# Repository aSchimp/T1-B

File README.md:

T1-B
====

T1-B = Turtle Bot 1

Installation
====

This *must* be run on a BeagleBone Black running the Debian operating system.  Get the latest image from: http://beagleboard.org/latest-images. The image used for testing was dated 2014-04-23. To check the version installed use

````
cat /boot/uboot/ID.txt
````

Make sure you can establish an SSH connection to the BeagleBone Black. Also make sure that the BBB has a persistant internet connection, either through an ethernet connection or through a USB connection to your computer.

### Setting up a persistant USB internet connection

The steps below are for Windows.

* Open the control panel, and search for "network connections" in the search box. Click "View Network Connections" in the results.
* Right-click the internet connection to share with the BeagleBone Black and select Properties. Navigate to the Sharing tab.
* Select the option to "Allow other network users to connect through this computer's Internet connection"
* Select the BeagleBone Black's network connection from the dropdown and then click OK.
* Now go back to Network Connections and right click the BeagleBone Black's network connection, and select Properties.
* Click "Internet Protocol Version 4 (TCP/IPv4)" in the list and select Properties
* Select the options to "Obtain an IP address automatically" and "obtain DNS server address automatically", and click OK

On the BeagleBone Black run the following commands

````
route add default gw 192.168.7.1
echo "nameserver 8.8.8.8" >> /etc/resolv.conf
````

Test the connection by running `ping google.com`.

Run the following command.

````
nano /opt/scripts/boot/am335x_evm.sh
````

Scroll down until you see the following lines

````
/sbin/ifconfig usb0 192.168.7.2 netmask 255.255.255.252
/usr/sbin/udhcpd -S /etc/udhcpd.conf
````

Immediately after those lines, add the following:

````
/sbin/route add default gw 192.168.7.1 metric 1
````

While you're editing that file, add the following line as well (beneath the line just added). This will allow the WiFi connection which will be setup by the installation script to work on startup. Replace 192.168.1.1 with the IP address of your router. You can find this by running `ipconfig` from a command prompt in Windows. Look for the default gateway for the wireless network connection.

````
/sbin/route add default gw 192.168.1.1 metric 2
````

Thanks to [Carl Lance](http://lanceme.blogspot.com/2013/06/windows-7-internet-sharing-for.html) for the pointers on getting this to work.

### Optionally Disable HDMI

TODO: Add an explanation here

https://learn.adafruit.com/setting-up-wifi-with-beaglebone-black/hardware

### Install Git

````
ntpdate -b -s -u pool.ntp.org
apt-get update && apt-get install git
````

### Install T1-B Software

Shutdown the BBB and plug in the USB wifi adapter. Use a WiFi adapter from [this list](http://www.elinux.org/Beagleboard:BeagleBoneBlack#WIFI_Adapters) for best results. The T1-B installation script has only been tested with the [NETGEAR N150 Wi-Fi USB Adapter (WNA1100)](http://www.amazon.com/gp/product/B0036R9XRU/ref=oh_aui_detailpage_o02_s00?ie=UTF8&psc=1). Turn the device back on.

Clone this repository into {TODO: determine best directory} using the following command.

````
cd {TODO: put directory here}
git clone https://github.com/aschimp/t1-b
````

Place your WiFi network SSID and password into the settings.cfg file.

````
cd t1-b/setup
nano settings.cfg
````

Finally, run the install script. The system will reboot several times during the installation. Log messages after rebooting will be sent to the install_log.txt file in the t1-b/setup directory.

````
chmod +x *.sh
./install.sh
````

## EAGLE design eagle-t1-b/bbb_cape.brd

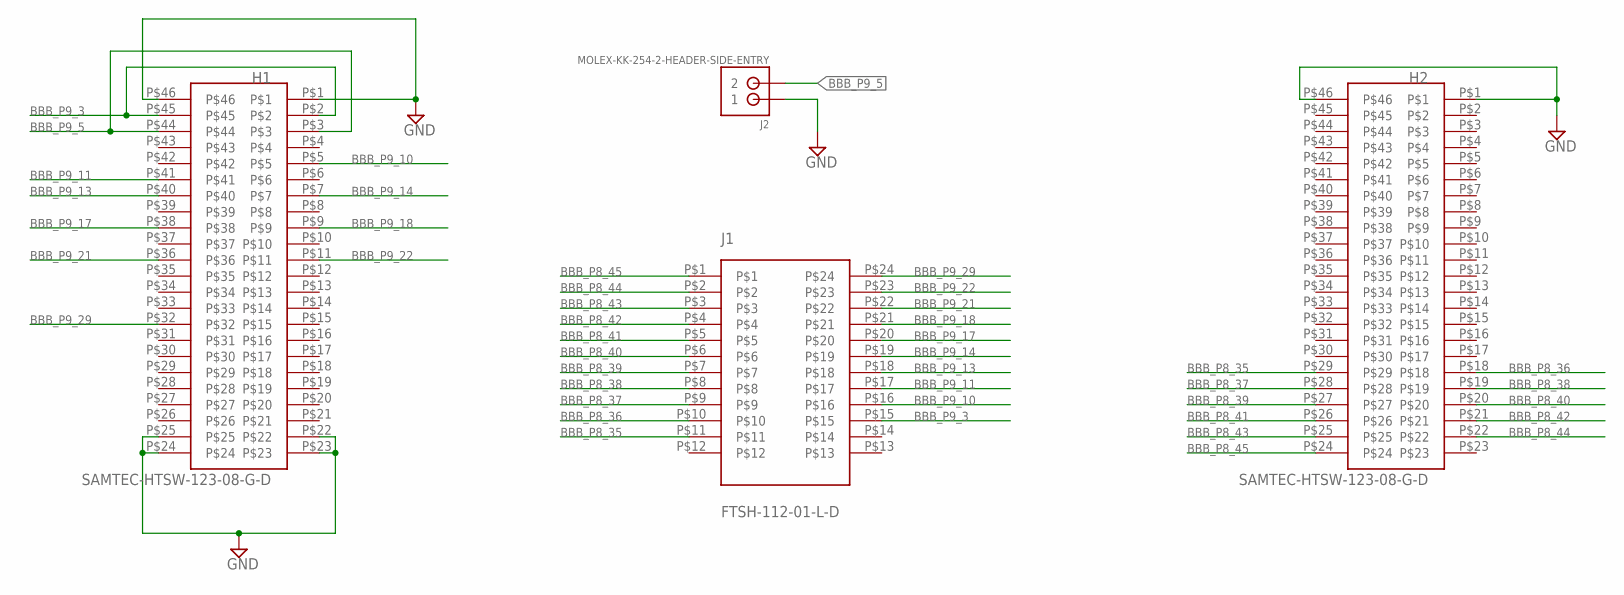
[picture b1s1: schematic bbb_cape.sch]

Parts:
H1, H2: SAMTEC-HTSW-123-08-G-D; HEADER-2X23-0.1-INCH
J1: FTSH-112-01-L-D
J2: MOLEX-KK-254-2-HEADER-SIDE-ENTRY

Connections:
BBB_P8_35: H2.P$29, J1.P$11
BBB_P8_36: H2.P$18, J1.P$10
BBB_P8_37: H2.P$28, J1.P$9
BBB_P8_38: H2.P$19, J1.P$8
BBB_P8_39: H2.P$27, J1.P$7
BBB_P8_40: H2.P$20, J1.P$6
BBB_P8_41: H2.P$26, J1.P$5
BBB_P8_42: H2.P$21, J1.P$4
BBB_P8_43: H2.P$25, J1.P$3
BBB_P8_44: H2.P$22, J1.P$2
BBB_P8_45: H2.P$24, J1.P$1
BBB_P9_3: H1.P$2, H1.P$45, J1.P$15
BBB_P9_5: H1.P$3, H1.P$44, J2.P$2 (2)
BBB_P9_10: H1.P$5, J1.P$16
BBB_P9_11: H1.P$41, J1.P$17
BBB_P9_13: H1.P$40, J1.P$18
BBB_P9_14: H1.P$7, J1.P$19
BBB_P9_17: H1.P$38, J1.P$20
BBB_P9_18: H1.P$9, J1.P$21
BBB_P9_21: H1.P$36, J1.P$22
BBB_P9_22: H1.P$11, J1.P$23
BBB_P9_29: H1.P$32, J1.P$24
GND: H1.P$1, H1.P$22, H1.P$23, H1.P$24, H1.P$25, H1.P$46, H2.P$1, H2.P$46, J2.P$1 (1)

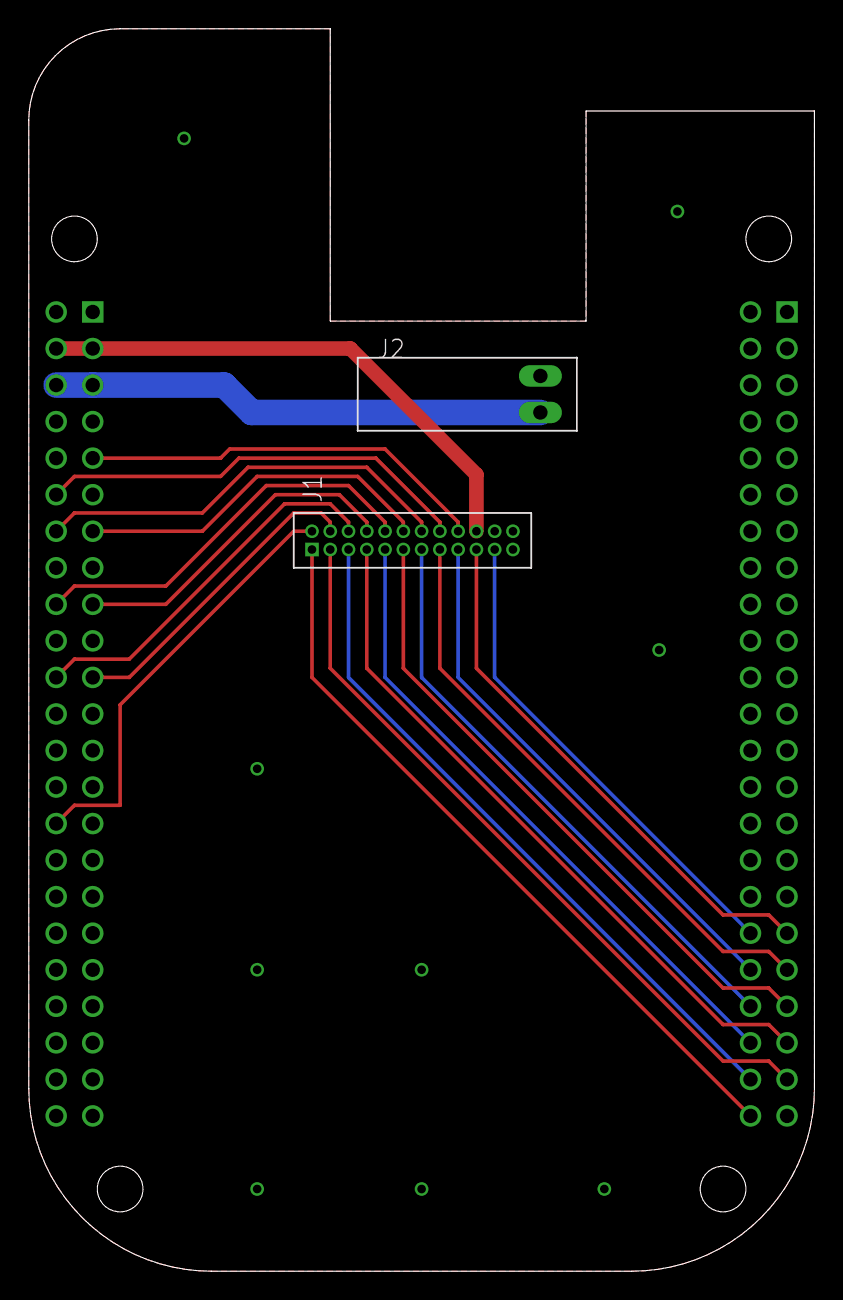
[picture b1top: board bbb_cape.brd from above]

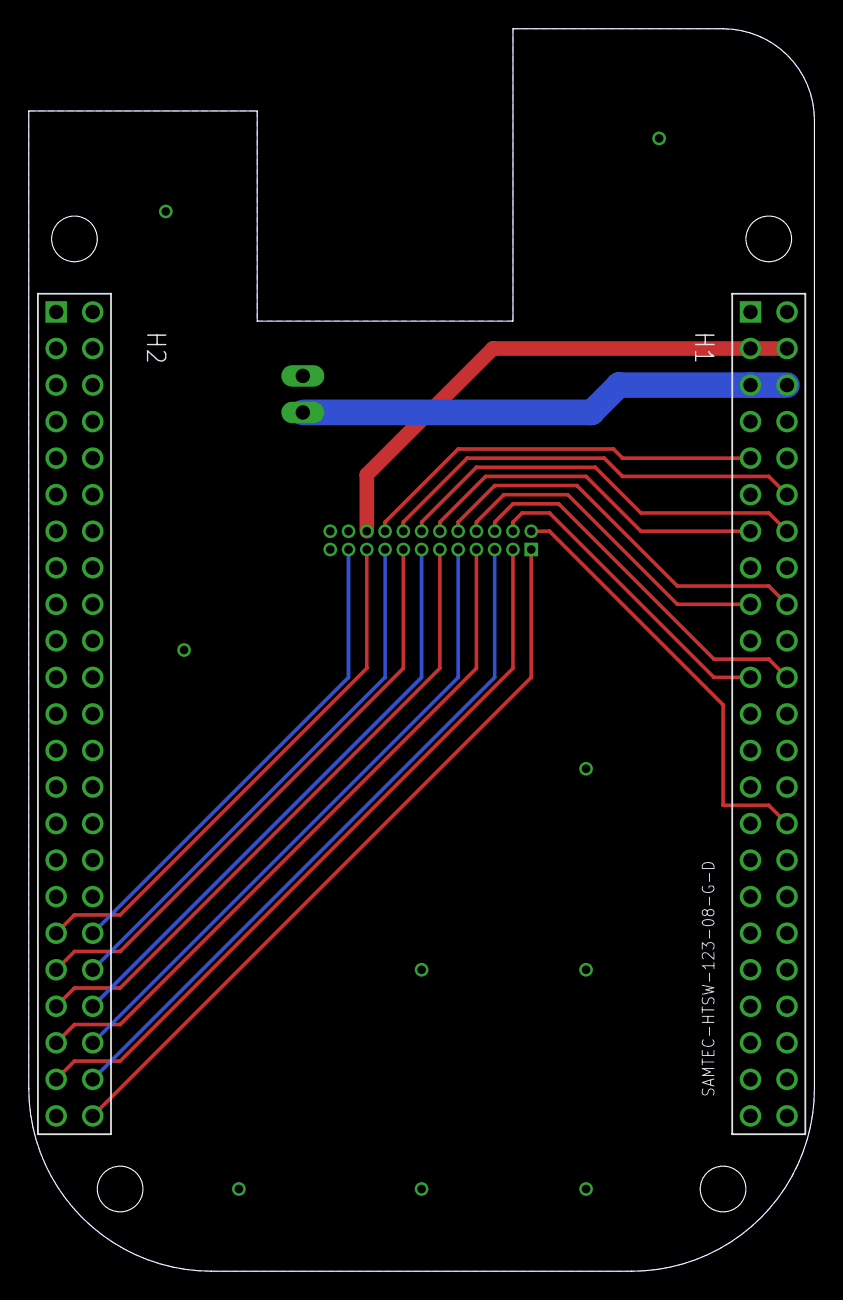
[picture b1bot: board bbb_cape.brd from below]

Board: 2 copper layers, 54.6 x 86.4 mm, 4 parts (2 on the bottom side), 23 nets.

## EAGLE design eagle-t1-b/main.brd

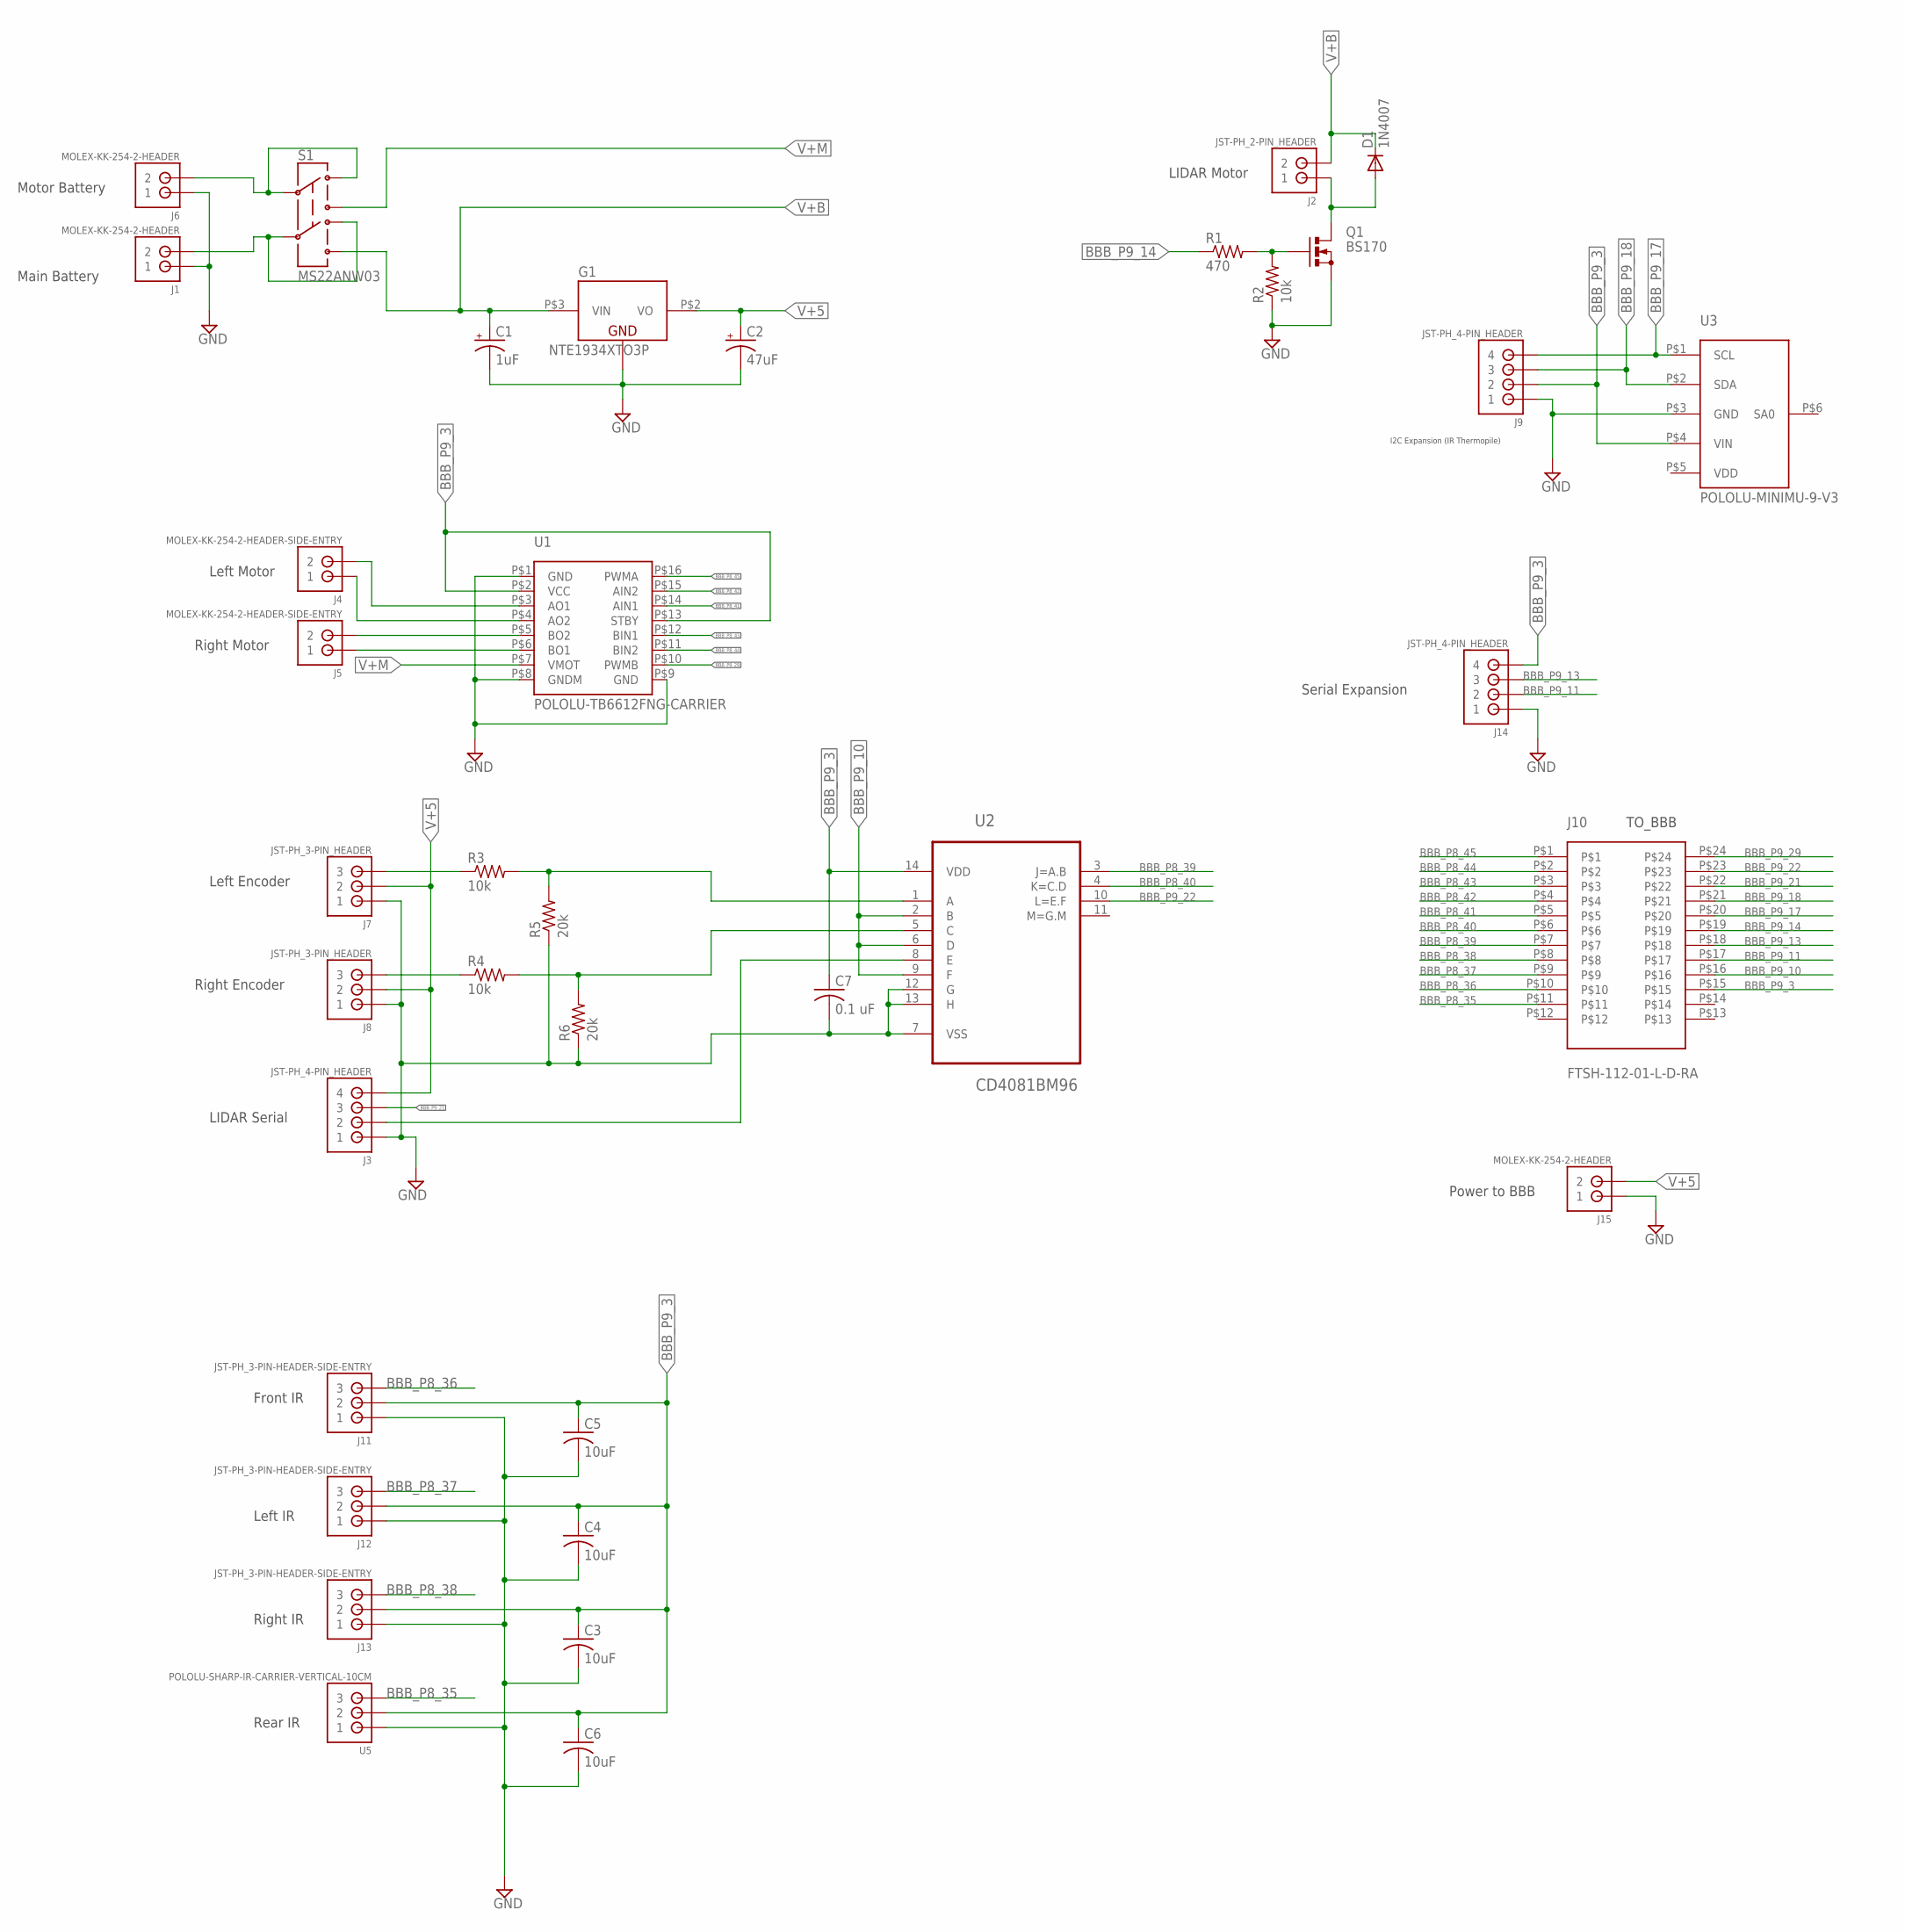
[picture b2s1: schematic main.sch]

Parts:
C1: 1uF; PANASONIC_B
C2: 47uF; PANASONIC_C
C3, C4, C5, C6: 10uF; C0603
C7: 0.1 uF; C0603
D1: 1N4007; DO41-10
G1: NTE1934XTO3P; TO3P
J1, J6, J15: MOLEX-KK-254-2-HEADER
J2: JST-PH_2-PIN_HEADER; JST_B2B-PH_HEADER
J3, J9, J14: JST-PH_4-PIN_HEADER; JST_B4B-PH_HEADER
J4, J5: MOLEX-KK-254-2-HEADER-SIDE-ENTRY
J7, J8: JST-PH_3-PIN_HEADER; JST_B3B-PH_HEADER
J10: FTSH-112-01-L-D-RA
J11, J12, J13: JST-PH_3-PIN-HEADER-SIDE-ENTRY; JST-S3B-PH-K-S
Q1: BS170; SOT54E
R1: 470; R0402
R2, R3, R4: 10k; R0402
R5, R6: 20k; R0402
S1: MS22ANW03; SWITCH-DPDT-NKK-MS22ANW03
U1: POLOLU-TB6612FNG-CARRIER
U2: CD4081BM96; SO14
U3: POLOLU-MINIMU-9-V3
U5: POLOLU-SHARP-IR-CARRIER-VERTICAL-10CM; POLOLU-SHARP-IR-CARRIER-VERTICAL-GP2Y0D8**Z0F

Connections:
BBB_P8_35: J10.P$11, U5.P$3 (3)
BBB_P8_36: J10.P$10, J11.P$3 (3)
BBB_P8_37: J10.P$9, J12.P$3 (3)
BBB_P8_38: J10.P$8, J13.P$3 (3)
BBB_P8_39: J10.P$7, U2.3 (J=A.B)
BBB_P8_39_AND_INPUT: R3.2, R5.2, U2.1 (A)
BBB_P8_40: J10.P$6, U2.4 (K=C.D)
BBB_P8_40_AND_INPUT: R4.2, R6.2, U2.5 (C)
BBB_P8_41: J10.P$5, U1.P$14 (AIN1)
BBB_P8_42: J10.P$4, U1.P$15 (AIN2)
BBB_P8_43: J10.P$3, U1.P$12 (BIN1)
BBB_P8_44: J10.P$2, U1.P$11 (BIN2)
BBB_P8_45: J10.P$1, U1.P$16 (PWMA)
BBB_P9_3: C3.1, C4.1, C5.1, C6.1, C7.1, J9.P2 (2), J10.P$15, J11.P$2 (2), J12.P$2 (2), J13.P$2 (2), J14.P4 (4), U1.P$2 (VCC), U1.P$13 (STBY), U2.14 (VDD), U3.P$4 (VIN), U5.P$2 (2)
BBB_P9_10: J10.P$16, U2.2 (B), U2.6 (D), U2.9 (F)
BBB_P9_11: J10.P$17, J14.P2 (2)
BBB_P9_13: J10.P$18, J14.P3 (3)
BBB_P9_14: J10.P$19, R1.1
BBB_P9_17: J9.P4 (4), J10.P$20, U3.P$1 (SCL)
BBB_P9_18: J9.P3 (3), J10.P$21, U3.P$2 (SDA)
BBB_P9_21: J3.P3 (3), J10.P$22
BBB_P9_22: J10.P$23, U2.10 (L=E.F)
BBB_P9_29: J10.P$24, U1.P$10 (PWMB)
GND: C1.-, C2.-, C3.2, C4.2, C5.2, C6.2, C7.2, G1.P$1 (GND), J1.P$1 (1), J3.P1 (1), J6.P$1 (1), J7.P1 (1), J8.P1 (1), J9.P1 (1), J11.P$1 (1), J12.P$1 (1), J13.P$1 (1), J14.P1 (1), J15.P$1 (1), Q1.S, R2.1, R5.1, R6.1, U1.P$1 (GND), U1.P$8 (GNDM), U1.P$9 (GND), U2.7 (VSS), U2.12 (G), U2.13 (H), U3.P$3 (GND), U5.P$1 (1)
unnamed: Q1.G, R1.2, R2.2
unnamed: D1.A, J2.P1 (1), Q1.D
unnamed: J5.P$1 (1), U1.P$6 (BO1)
unnamed: J5.P$2 (2), U1.P$5 (BO2)
unnamed: J4.P$1 (1), U1.P$4 (AO2)
unnamed: J4.P$2 (2), U1.P$3 (AO1)
unnamed: J7.P3 (3), R3.1
unnamed: J6.P$2 (2), S1.P$1 (1), S1.P$2 (2)
unnamed: J1.P$2 (2), S1.P$4 (4), S1.P$5 (5)
unnamed: J8.P3 (3), R4.1
unnamed: J3.P2 (2), U2.8 (E)
V+5: C2.+, G1.P$2 (VO), J3.P4 (4), J7.P2 (2), J8.P2 (2), J15.P$2 (2)
V+B: C1.+, D1.C, G1.P$3 (VIN), J2.P2 (2), S1.P$6 (6)
V+M: S1.P$3 (3), U1.P$7 (VMOT)
VDD: U3.P$5 (VDD)

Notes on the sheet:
Left Motor
Right Motor
Motor Battery
Main Battery
Left Encoder
Right Encoder
LIDAR Serial
LIDAR Motor
I2C Expansion (IR Thermopile)
TO_BBB
Serial Expansion
Front IR
Left IR
Right IR
Rear IR
Power to BBB

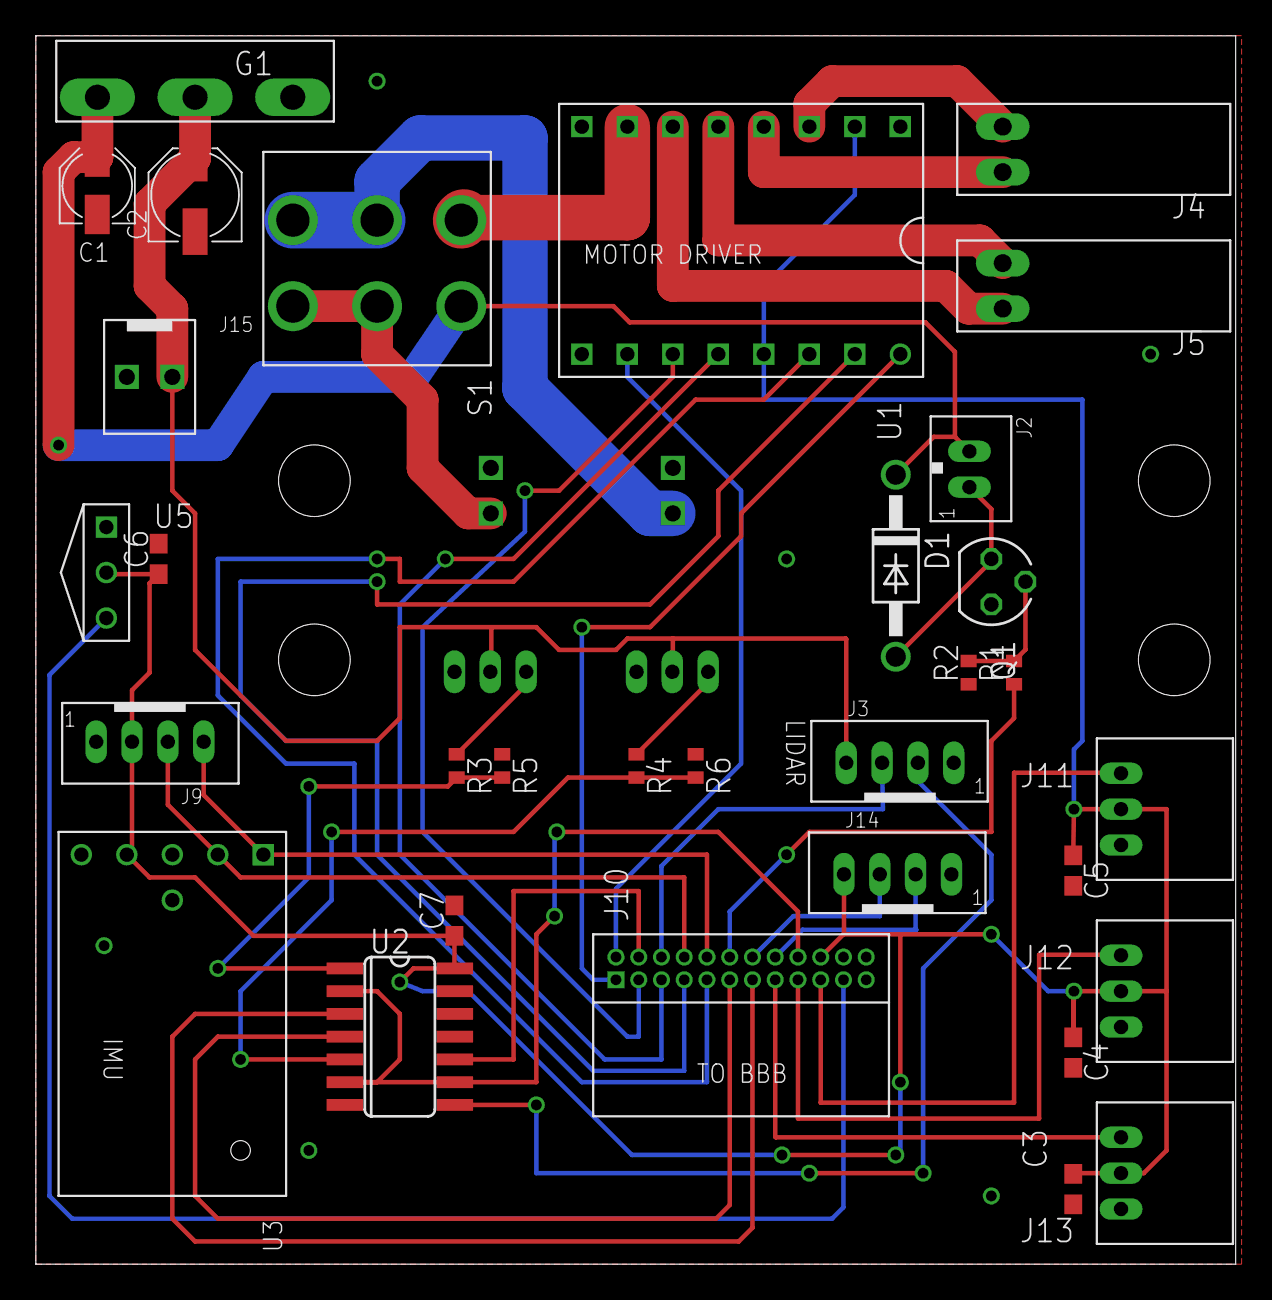
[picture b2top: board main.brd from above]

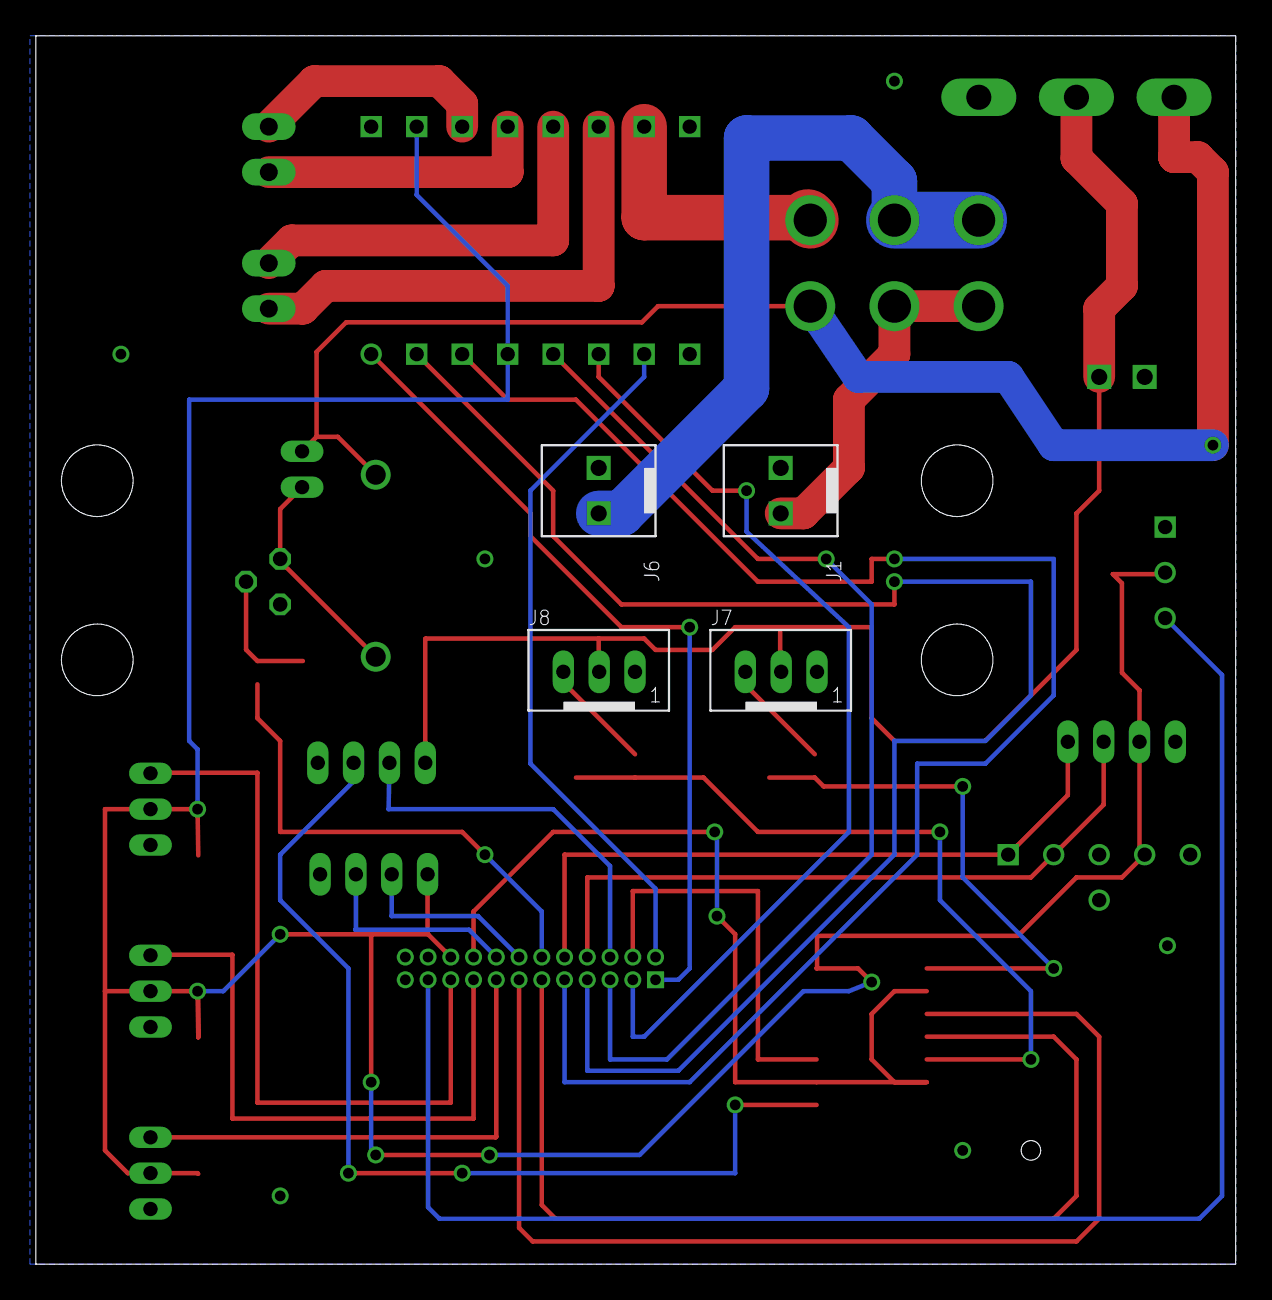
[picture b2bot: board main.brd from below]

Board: 2 copper layers, 67.0 x 68.6 mm, 36 parts (4 on the bottom side), 38 nets.

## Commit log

2014-10-26 Added installation scripts (not finished yet) and python script for reading lidar data (also not finished yet
2014-10-26 Added misc experimental files
2014-10-26 Updated README.md with installation instructions
2015-10-18 Transferring code from bbb-sockets-test to jump-start T1-B's code.
2015-10-25 Added schematic for main board.
2015-10-28 Added intitialization script for right drive encoder and infrared proximity sensor input pins.
2015-10-29 Adding i2c nodejs package.
2015-10-30 Switching from i2c to i2c-bus
2015-10-30 Added init script for IMU I2C device tree overlay.
2015-10-30 Added exec permission to initialize_io.sh
2015-11-01 Increased default pwm duty cycle for lidar motor now that it is being powered from 9.6 volts
2015-11-07 Finished main board schematic and pcb layout.
2015-11-07 Added init script for extra serial port (commented out).
2015-11-26 Finalized circuit board designs.
2015-11-26 Reversing motor rotation.
